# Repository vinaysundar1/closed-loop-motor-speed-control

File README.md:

# PID Motor Speed Controller

Closed-loop DC motor speed control using a quadrature encoder for feedback and a PID
algorithm to hold a target RPM, running on an Arduino Uno. Custom PCB designed in
KiCad, hand-soldered and assembled into a complete PCBA.
[github.com/vinaysundar1/closed-loop-motor-speed-control](https://github.com/vinaysundar1/closed-loop-motor-speed-control)

*Finished PCBA — Arduino, DRV8871 driver, barrel jack, and encoder/OLED/potentiometer
headers, hand-soldered and assembled.*

*Kp=0.5, Ki=0.5, Kd=0.08 — settles within one overshoot/undershoot cycle (~157 RPM
peak, ~90 RPM trough) and holds steady at setpoint.*

## Results

With a live, continuously-varying setpoint (driven by a potentiometer rather than a
fixed step), the controller tracks a ramping target with **one damped
overshoot/undershoot cycle** before settling, and holds within roughly **±2 RPM of
setpoint at steady state**.

## Hardware

| Component | Details |
|---|---|
| Arduino Uno | Microcontroller |
| L298N H-Bridge | Motor driver |
| DC motor with rotary encoder | GA25-370, 12V, 500 RPM nominal |
| 0.96" OLED display (SSD1306) | I2C status display |
| 10K potentiometer | Setpoint dial |
| 12V power supply or battery pack | Motor power |
| Breadboard + jumper wires | — |

## System Block Diagram

```mermaid
flowchart LR
    P[Potentiometer<br/>Setpoint Dial] -->|analog read,<br/>mapped 0-400 RPM| A[Setpoint]
    A --> B((Sum))
    F[Encoder Feedback] --> B
    B -->|error| C[PID Controller]
    C -->|PWM 0-255| D[Motor Driver / H-Bridge]
    D --> E[DC Gear Motor]
    E -->|shaft rotation| F
    E --> G[OLED Display]
    A --> G
```

## How It Works

1. **Speed measurement:** A hardware interrupt counts encoder pulses on every rising
   edge. Every 100 ms, the tick count is converted to RPM:
   `RPM = (ticks / PPR) * (60000 / interval_ms)`
2. **Noise filtering:** Raw RPM is smoothed with an exponential moving average (EMA)
   before being used anywhere else in the loop, since tick-count-based measurement
   over a short window is inherently noisy.
3. **PID calculation:** Standard proportional + integral + derivative sum, with:
   - A second EMA filter applied specifically to the derivative term (derivative
     amplifies noise more than any other term).
   - Conditional-integration anti-windup — the integral only accumulates when doing
     so wouldn't push the output past the PWM actuator limits (0–255).
4. **Actuation:** Final PID output is clamped to 0–255 (the PID math itself has no
   upper or lower bound, but `analogWrite` only accepts an 8-bit PWM duty cycle, so
   the raw sum has to be forced into the range the hardware can actually accept) and
   written via `analogWrite` to the motor driver's PWM input.

## Tuning Process

**Initial attempt** — naive PID with unfiltered RPM feedback:

*Kp=0.6, Ki=0.1, Kd=0.05 — oscillation amplitude grows over time rather than settling*

Diagnosis: the derivative term was amplifying tick-count measurement noise (division
by a small `dt` multiplies noise), and the integral anti-windup only clamped the
final value rather than preventing over-accumulation during saturation, both
contributing to a sustained/growing limit cycle.

**Fix:** added EMA filtering on the RPM measurement and on the derivative term, and
switched to conditional-integration anti-windup.

*Kp=1.0, Ki=0.08, Kd=0.02 — clean damped response, but settles ~30 RPM below setpoint*

Diagnosis: proportional control alone cannot fully close steady-state error against
real motor friction/load, that gap can only be closed by the integral term, and Ki
was too small to close it in a reasonable time.

**Increased Ki to close the steady-state gap:**

*Kp=1.0, Ki=0.75, Kd=0.02 — closes the steady-state gap, but rings through roughly two
decaying overshoot/undershoot cycles before settling*

**Isolating the double-oscillation:** to find the cause, Kp was held fixed at 1.0
while Ki and Kd were varied independently across several tests (Ki: 0.75 → 0.35 → 0.5;
Kd: 0.02 → 0.2 → 0.08). The first overshoot peak stayed essentially unchanged
(~205–233 RPM) across every one of these combinations — strong evidence that Kp, not
Ki or Kd, was driving the size of that first overshoot, since neither term had moved
it despite multiple independent tests.

**Note on Ki tuning:** I also tested higher Ki values (up to 1.0) to see if faster settling was worth the tradeoff. Higher Ki consistently reduced settling time but increased overshoot (up to ~172 RPM vs. the original ~157 RPM), and increasing Kd alongside it didn't meaningfully reduce that overshoot. I kept Kp=0.5, Ki=0.5, Kd=0.08 as the final configuration since it produced the smallest overshoot/undershoot swings, which I prioritized over faster settling for this system.

**Final tune:** lowered Kp itself (1.0 → 0.6 → 0.5), keeping Ki=0.5 and Kd=0.08 fixed.
The first overshoot dropped sharply with each reduction (≈205 → 170 → 157 RPM), while
the undershoot depth stayed roughly constant (~90–100 RPM) regardless of Kp.

*Kp=0.5, Ki=0.5, Kd=0.08 — settles after one overshoot/undershoot cycle (~157 RPM peak,
~90 RPM trough), then a smooth, non-oscillatory approach to setpoint*

## Live Setpoint via Potentiometer

The initial tuning above used a fixed, hardcoded setpoint (150 RPM) for a clean,
repeatable step-response test. Once the gains were validated, the setpoint was
switched to a potentiometer read on an analog pin, mapped to a 0–400 RPM range, so
the target speed can be changed live by turning a knob.

A moving setpoint introduces failure modes a fixed step test doesn't expose:

- **Small electrical noise on the analog reading** caused the setpoint to
  flicker by a couple RPM every loop, which would look like a disturbance to the
  derivative term. Fixed with a deadband: the setpoint only updates if the
  new reading differs from the current one by more than 3 RPM.

*Kp=0.5, Ki=0.5, Kd=0.08 — RPM (orange) tracks a setpoint (green) jump, with one overshoot to one undershoot before settling and
holding steady-state tracking at the new target*

## Final PID Gains

| Gain | Value | Purpose |
|---|---|---|
| Kp | 0.5 | Primary response to instantaneous error; lowered from an initial 1.0 after isolating it as the driver of first-overshoot magnitude |
| Ki | 0.5 | Eliminates steady-state error from motor friction/load |
| Kd | 0.08 | Damps overshoot; raised from an initial 0.02 now that the derivative acts on a filtered signal |

## PCB Design

The breadboard prototype below was translated into a custom PCB in KiCad,
consolidating the Arduino, motor driver, and peripheral connections into a single
soldered board with defined connector headers.

*v1 — breadboard prototype: Arduino Uno, L298N motor driver, GA25-370 encoder motor,
potentiometer, and OLED display.*

*Full schematic — Arduino header, DRV8871 motor driver with support circuitry,
barrel jack power input, and connector headers for the encoder, OLED, and
potentiometer.*

### Current-Limit (ILIM) Resistor

The DRV8871 sets its current limit via a resistor from ILIM to GND, per the
datasheet relationship ITRIP ≈ 64,000 / R_ILIM(Ω). The GA25-370's rated block/stall
current is 1.1A; a 32kΩ resistor was chosen to set a ~2A limit, giving roughly 2x
margin above the motor's normal stall current so the limit protects against
faults without nuisance-tripping during normal operation.

### Decoupling

A 0.1µF ceramic capacitor (high-frequency switching noise) and a 47µF electrolytic
capacitor (bulk current supply during motor transients) are placed across VM/GND,
matching TI's reference application circuit for this driver.

### Power Trace Sizing

Trace widths were calculated using KiCad's built-in IPC-2221 calculator:

| Net class | Current basis | Calculated minimum | Used |
|---|---|---|---|
| Power (VMOTOR, GND, motor outputs) | 2A (ILIM-protected worst case), 10°C rise | ~30.8 mil | 32 mil |
| Signal (I2C, control inputs, ILIM) | 1A reference, 10°C rise | ~12 mil | 12 mil |

*Routed PCB layout — 0.8mm power traces (VMOTOR/GND/motor outputs), 0.3mm signal
traces, ground pour on the bottom layer with thermal vias under the driver IC.*

*Bench bring-up — the assembled PCBA connected to the motor, encoder, and OLED
during initial power-on testing, confirming the board functions as designed
before final wiring cleanup.*

## Lessons Learned

- Sensor noise, not just gain values, can be the root cause of oscillation.
  Filtering the measurement is important in the tuning process.
- Anti-windup implementation matters: clamping the integral's final value is not the
  same as preventing it from over-accumulating in the first place.
- Empirical calibration (measuring encoder PPR directly) caught an incorrect
  assumption that a spec-sheet/datasheet number would have missed.
- Isolating one gain at a time was
  what actually revealed which gain caused which symptom. Multiple tests where Ki
  and Kd changed with no effect on the first overshoot were what pointed to Kp as
  the real cause, rather than guessing.

## Future Improvements

- Reset the integral term on large setpoint jumps, so accumulated history from the
  old target doesn't bleed into the transient response at a new one
- Quadrature (2-channel) decoding for direction sensing and 4x resolution
- Auto-tuning via relay/Ziegler-Nichols method triggered by a button press
- Using more precise motors and potentiometers to reduce error.

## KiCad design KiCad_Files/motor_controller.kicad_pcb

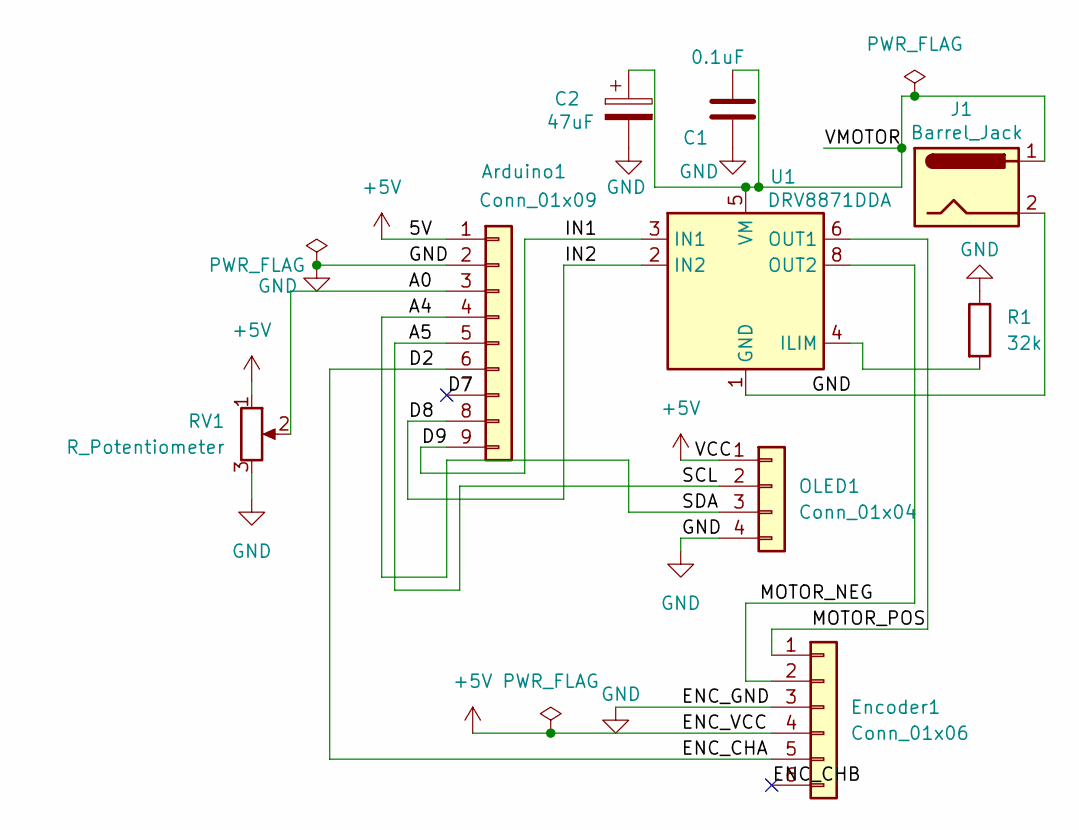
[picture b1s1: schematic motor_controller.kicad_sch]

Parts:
Arduino1: Conn_01x09; PinHeader_1x09_P2.54mm_Vertical
C1: 0.1uF; C_Disc_D5.0mm_W2.5mm_P5.00mm
C2: 47uF; CP_Radial_D6.3mm_P2.50mm
Encoder1: Conn_01x06; PinHeader_1x06_P2.54mm_Vertical
J1: Barrel_Jack; BarrelJack_Wuerth_694108106102_2.5x5.5mm
OLED1: Conn_01x04; PinHeader_1x04_P2.54mm_Vertical
R1: 32k; R_Axial_DIN0207_L6.3mm_D2.5mm_P10.16mm_Horizontal
RV1: R_Potentiometer; Potentiometer_Bourns_3386P_Vertical
U1: DRV8871DDA; Texas_HTSOP-8-1EP_3.9x4.9mm_P1.27mm_EP2.95x4.9mm_Mask2.4x3.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

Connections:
+5V: Arduino1.1, Encoder1.4, OLED1.1, RV1.1
/A0: Arduino1.3, RV1.2
/A4: Arduino1.4, OLED1.3
/A5: Arduino1.5, OLED1.2
/D2: Arduino1.6, Encoder1.5
/D7: Arduino1.7
/D8: Arduino1.8, U1.2 (IN2)
/D9: Arduino1.9, U1.3 (IN1)
/ENC_CHB: Encoder1.6
/MOTOR_NEG: Encoder1.2, U1.8 (OUT2)
/MOTOR_POS: Encoder1.1, U1.6 (OUT1)
/VMOTOR: C1.2, C2.1, J1.1, U1.5 (VM)
GND: Arduino1.2, C1.1, C2.2, Encoder1.3, J1.2, OLED1.4, R1.1, RV1.3, U1.1 (GND), U1.7 (GND), U1.9 (GND)
unnamed: R1.2, U1.4 (ILIM)

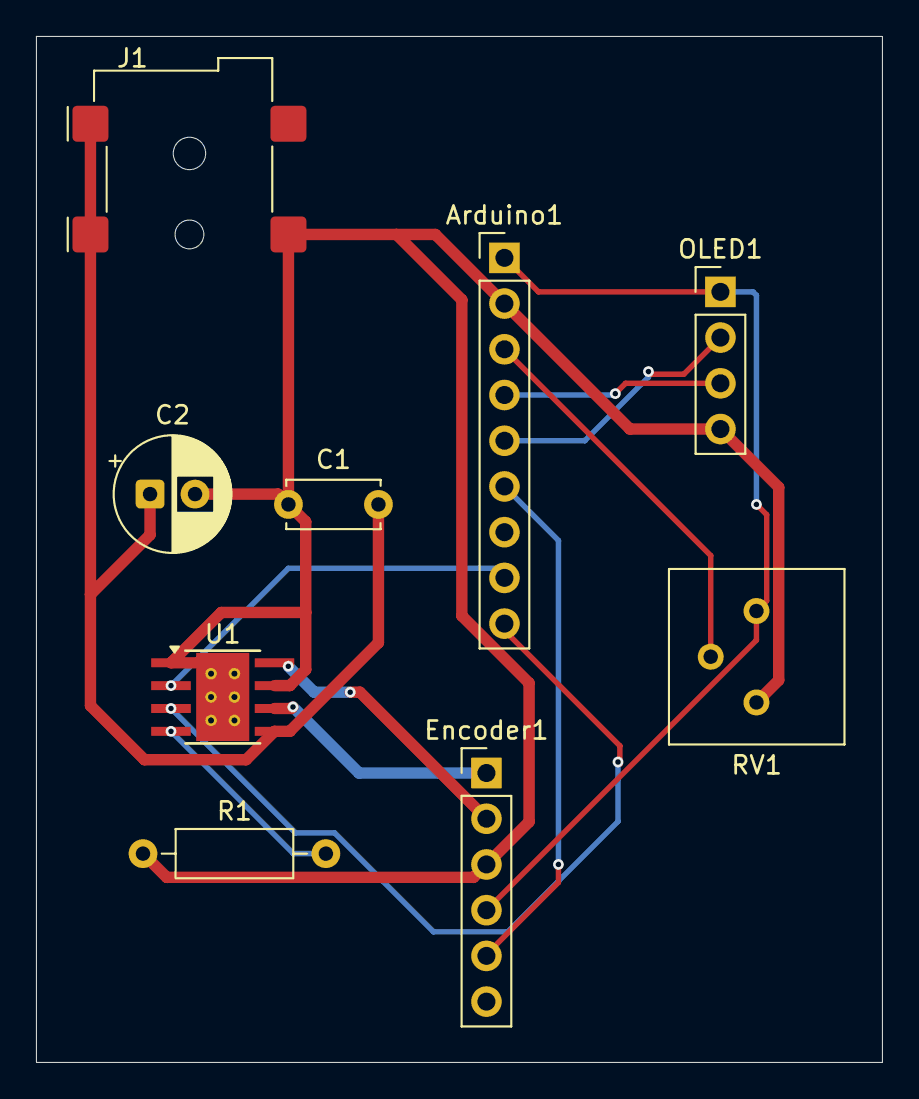
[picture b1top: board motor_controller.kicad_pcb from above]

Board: 2 copper layers, 47.0 x 57.0 mm, 9 parts (0 on the bottom side), 12 nets.
